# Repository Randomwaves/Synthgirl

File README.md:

# Synthgirl

**A touch-controlled hardware wavetable synthesizer** — dual-oscillator synth engine and DSP effects built around an STM32H723 (Cortex-M7), with a 480×854 color display, a fully capacitive-touch control surface, and MIDI/Sync I/O.

This repository holds the complete hardware design (Eagle/KiCad) and firmware (STM32CubeIDE / C++) for Synthgirl, released by [Randomwaves](https://randomwaves.io) as an open hardware/software project. Synthgirl shares its platform, DSP chain, and touch-based control surface with [Drumboy](https://github.com/Randomwaves/Drumboy), built around a dual-oscillator wavetable engine instead of a sample-layer sequencer.

---

## Overview

The MCU sits at the center of the same core subsystems as Drumboy: an NT35510 display over a 16-bit parallel GPIO bus, external SDRAM on the FMC bus for wavetable storage, an SGTL5000 audio codec over I2S/I2C, a microSD card over SDMMC2 for storage, and MIDI/Sync connectivity over USART/GPIO. The control surface is driven entirely by three capacitive-touch channels.

| | |
|---|---|
| **MCU** | STM32H723ZGT6 — Cortex-M7, LQFP-144 |
| **Display** | NT35510, 480×854, 16-bit parallel |
| **SDRAM** | External, FMC bus (wavetable storage) |
| **Audio codec** | SGTL5000 — I2S3 audio / I2C3 control |
| **Storage** | microSD, SDMMC2, FAT filesystem |
| **Control surface** | 3× capacitive-touch channels (CT0–CT2) |
| **Connectivity** | MIDI In/Out, Sync In/Out |
| **Firmware** | v1.05 |

## Features

- **Dual-oscillator wavetable engine** (Osc A / Osc B), each with independent LFO modulation
- **9 effect types** per send slot: Delay, Chorus, Flanger, Phaser, Compressor, Expander, Overdrive, Distortion, Bitcrusher
- **2 multimode filters + 2 send effects + stereo reverb** in the DSP chain
- **Built-in step sequencer** alongside live/MIDI note input
- **MIDI In/Out** and **Sync In/Out** for external clock/gate sync
- **SD-card firmware updates** via a dedicated bootloader, mirroring the same two-project split as Drumboy

## Repository structure

```
01 Hardware/
  Main/       Main board — Eagle CAD (Main.sch / Main.brd)
  Top/        Top/control-surface board — Eagle CAD (Top.sch / Top.brd)
  Connector/  Interconnect board — KiCad (migrated from Eagle)
  Bottom/     Base board — KiCad (migrated from Eagle)

02 Software/
  Synthgirl-Boot-H723/   Bootloader — STM32CubeIDE project
  Synthgirl-App-H723/    Application firmware — STM32CubeIDE project
  Firmware/               Prebuilt firmware binaries
  Sd Card/                Reference SD card contents (wavetables, presets, system data)
```

## Hardware

Main and Top were originally designed in **Autodesk Eagle** (`.sch` / `.brd`); Connector and Bottom have since been migrated to **KiCad**.

## Firmware

Built with **STM32CubeIDE**, written in C/C++ against the STM32 HAL. Firmware is split into `Synthgirl-Boot-H723` (bootloader) and `Synthgirl-App-H723` (application), sharing one flash device — the same split used across Randomwaves' STM32H723 instruments.

## License

Released under the [MIT License](LICENSE).

## Community

- 💬 [Discord community](https://discord.gg/5atevNH6UU) — join the discussion
- 🌐 [randomwaves.io](https://www.randomwaves.io)
- ✉️ [hello@randomwaves.io](mailto:hello@randomwaves.io)

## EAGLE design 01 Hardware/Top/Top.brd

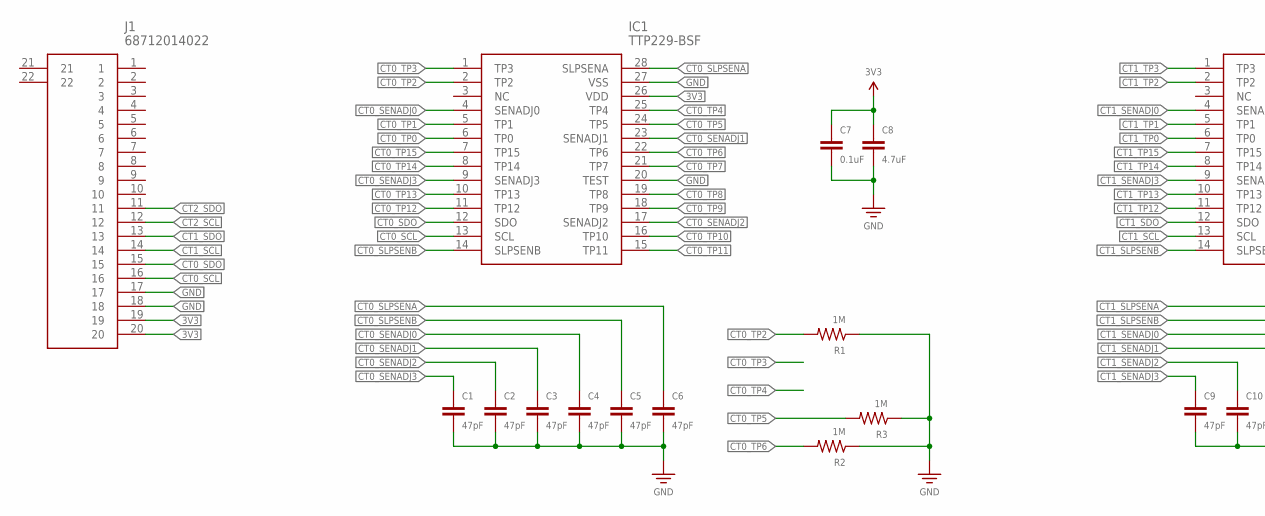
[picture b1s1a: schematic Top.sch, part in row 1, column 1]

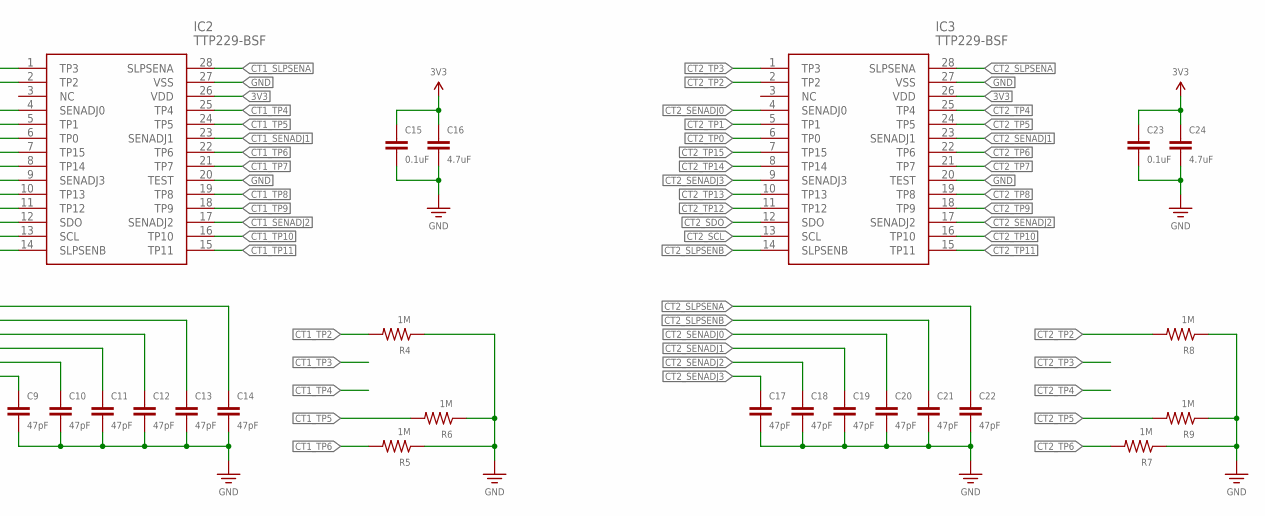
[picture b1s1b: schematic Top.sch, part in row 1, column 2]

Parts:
C1, C2, C3, C4, C5, C6, C9, C10, C11, C12, C13, C14, C17, C18, C19, C20, C21, C22: 47pF; CAP-0603
C7, C15, C23: 0.1uF; CAP-0603
C8, C16, C24: 4.7uF; CAP-0603
IC1, IC2, IC3: TTP229-BSF; SOP64P600X175-28N
J1: 68712014022
R1, R2, R3, R4, R5, R6, R7, R8, R9: 1M; RES-0603

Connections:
3V3: C7.P$1 (1), C8.P$1 (1), C15.P$1 (1), C16.P$1 (1), C23.P$1 (1), C24.P$1 (1), IC1.26 (VDD), IC2.26 (VDD), IC3.26 (VDD), J1.19, J1.20
CT0_SCL: IC1.13 (SCL), J1.16
CT0_SDO: IC1.12 (SDO), J1.15
CT0_SENADJ0: C4.P$1 (1), IC1.4 (SENADJ0)
CT0_SENADJ1: C3.P$1 (1), IC1.23 (SENADJ1)
CT0_SENADJ2: C2.P$1 (1), IC1.17 (SENADJ2)
CT0_SENADJ3: C1.P$1 (1), IC1.9 (SENADJ3)
CT0_SLPSENA: C6.P$1 (1), IC1.28 (SLPSENA)
CT0_SLPSENB: C5.P$1 (1), IC1.14 (SLPSENB)
CT0_TP0: IC1.6 (TP0)
CT0_TP1: IC1.5 (TP1)
CT0_TP2: IC1.2 (TP2), R1.P$2 (2)
CT0_TP3: IC1.1 (TP3)
CT0_TP4: IC1.25 (TP4)
CT0_TP5: IC1.24 (TP5), R3.P$2 (2)
CT0_TP6: IC1.22 (TP6), R2.P$2 (2)
CT0_TP7: IC1.21 (TP7)
CT0_TP8: IC1.19 (TP8)
CT0_TP9: IC1.18 (TP9)
CT0_TP10: IC1.16 (TP10)
CT0_TP11: IC1.15 (TP11)
CT0_TP12: IC1.11 (TP12)
CT0_TP13: IC1.10 (TP13)
CT0_TP14: IC1.8 (TP14)
CT0_TP15: IC1.7 (TP15)
CT1_SCL: IC2.13 (SCL), J1.14
CT1_SDO: IC2.12 (SDO), J1.13
CT1_SENADJ0: C12.P$1 (1), IC2.4 (SENADJ0)
CT1_SENADJ1: C11.P$1 (1), IC2.23 (SENADJ1)
CT1_SENADJ2: C10.P$1 (1), IC2.17 (SENADJ2)
CT1_SENADJ3: C9.P$1 (1), IC2.9 (SENADJ3)
CT1_SLPSENA: C14.P$1 (1), IC2.28 (SLPSENA)
CT1_SLPSENB: C13.P$1 (1), IC2.14 (SLPSENB)
CT1_TP0: IC2.6 (TP0)
CT1_TP1: IC2.5 (TP1)
CT1_TP2: IC2.2 (TP2), R4.P$2 (2)
CT1_TP3: IC2.1 (TP3)
CT1_TP4: IC2.25 (TP4)
CT1_TP5: IC2.24 (TP5), R6.P$2 (2)
CT1_TP6: IC2.22 (TP6), R5.P$2 (2)
CT1_TP7: IC2.21 (TP7)
CT1_TP8: IC2.19 (TP8)
CT1_TP9: IC2.18 (TP9)
CT1_TP10: IC2.16 (TP10)
CT1_TP11: IC2.15 (TP11)
CT1_TP12: IC2.11 (TP12)
CT1_TP13: IC2.10 (TP13)
CT1_TP14: IC2.8 (TP14)
CT1_TP15: IC2.7 (TP15)
CT2_SCL: IC3.13 (SCL), J1.12
CT2_SDO: IC3.12 (SDO), J1.11
CT2_SENADJ0: C20.P$1 (1), IC3.4 (SENADJ0)
CT2_SENADJ1: C19.P$1 (1), IC3.23 (SENADJ1)
CT2_SENADJ2: C18.P$1 (1), IC3.17 (SENADJ2)
CT2_SENADJ3: C17.P$1 (1), IC3.9 (SENADJ3)
CT2_SLPSENA: C22.P$1 (1), IC3.28 (SLPSENA)
CT2_SLPSENB: C21.P$1 (1), IC3.14 (SLPSENB)
CT2_TP0: IC3.6 (TP0)
CT2_TP1: IC3.5 (TP1)
CT2_TP2: IC3.2 (TP2), R8.P$2 (2)
CT2_TP3: IC3.1 (TP3)
CT2_TP4: IC3.25 (TP4)
CT2_TP5: IC3.24 (TP5), R9.P$2 (2)
CT2_TP6: IC3.22 (TP6), R7.P$2 (2)
CT2_TP7: IC3.21 (TP7)
CT2_TP8: IC3.19 (TP8)
CT2_TP9: IC3.18 (TP9)
CT2_TP10: IC3.16 (TP10)
CT2_TP11: IC3.15 (TP11)
CT2_TP12: IC3.11 (TP12)
CT2_TP13: IC3.10 (TP13)
CT2_TP14: IC3.8 (TP14)
CT2_TP15: IC3.7 (TP15)
GND: C1.P$2 (2), C2.P$2 (2), C3.P$2 (2), C4.P$2 (2), C5.P$2 (2), C6.P$2 (2), C7.P$2 (2), C8.P$2 (2), C9.P$2 (2), C10.P$2 (2), C11.P$2 (2), C12.P$2 (2), C13.P$2 (2), C14.P$2 (2), C15.P$2 (2), C16.P$2 (2), C17.P$2 (2), C18.P$2 (2), C19.P$2 (2), C20.P$2 (2), C21.P$2 (2), C22.P$2 (2), C23.P$2 (2), C24.P$2 (2), IC1.20 (TEST), IC1.27 (VSS), IC2.20 (TEST), IC2.27 (VSS), IC3.20 (TEST), IC3.27 (VSS), J1.17, J1.18, R1.P$1 (1), R2.P$1 (1), R3.P$1 (1), R4.P$1 (1), R5.P$1 (1), R6.P$1 (1), R7.P$1 (1), R8.P$1 (1), R9.P$1 (1)

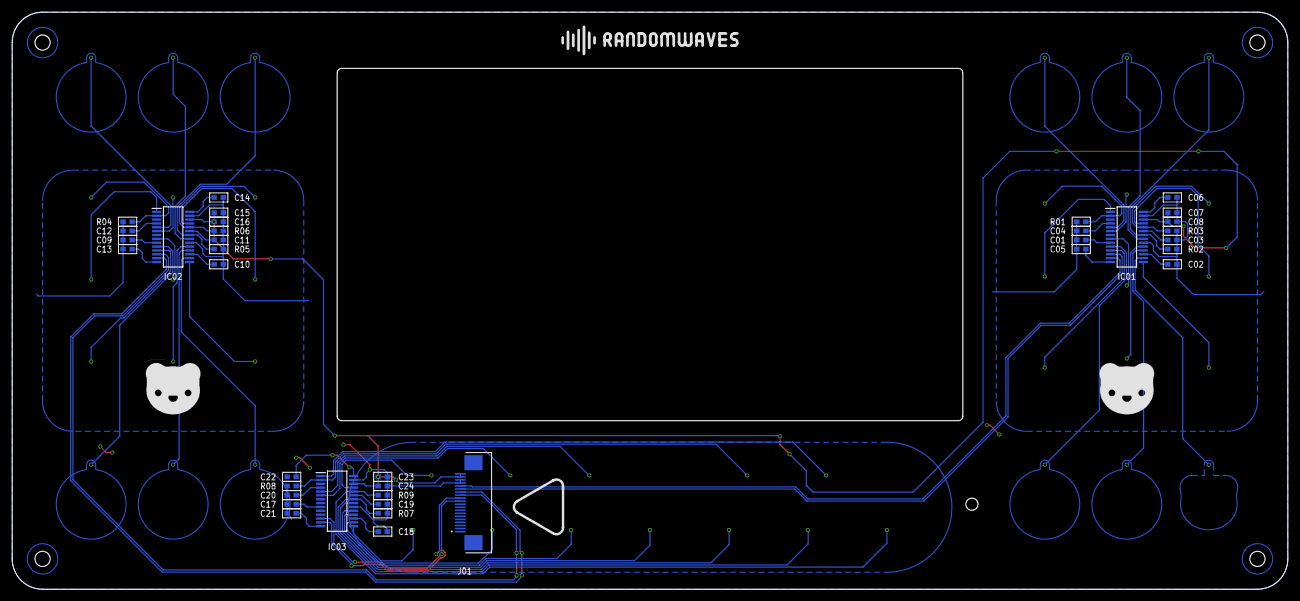
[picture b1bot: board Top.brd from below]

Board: 2 copper layers, 210.0 x 95.0 mm, 37 parts (37 on the bottom side), 35 nets.

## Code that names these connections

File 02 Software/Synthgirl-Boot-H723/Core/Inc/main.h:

/* USER CODE BEGIN Header */
/**
  ******************************************************************************
  * @file           : main.h
  * @brief          : Header for main.c file.
  *                   This file contains the common defines of the application.
  ******************************************************************************
  * @attention
  *
  * Copyright (c) 2023 STMicroelectronics.
  * All rights reserved.
  *
  * This software is licensed under terms that can be found in the LICENSE file
  * in the root directory of this software component.
  * If no LICENSE file comes with this software, it is provided AS-IS.
  *
  ******************************************************************************
  */
/* USER CODE END Header */

/* Define to prevent recursive inclusion -------------------------------------*/
#ifndef __MAIN_H
#define __MAIN_H

#ifdef __cplusplus
extern "C" {
#endif

/* Includes ------------------------------------------------------------------*/
#include "stm32h7xx_hal.h"

/* Private includes ----------------------------------------------------------*/
/* USER CODE BEGIN Includes */

/* USER CODE END Includes */

/* Exported types ------------------------------------------------------------*/
/* USER CODE BEGIN ET */

/* USER CODE END ET */

/* Exported constants --------------------------------------------------------*/
/* USER CODE BEGIN EC */

/* USER CODE END EC */

/* Exported macro ------------------------------------------------------------*/
/* USER CODE BEGIN EM */

/* USER CODE END EM */

/* Exported functions prototypes ---------------------------------------------*/
void Error_Handler(void);

/* USER CODE BEGIN EFP */

/* USER CODE END EFP */

/* Private defines -----------------------------------------------------------*/
#define CT2_SCL_Pin GPIO_PIN_2
#define CT2_SCL_GPIO_Port GPIOE
#define SDMMC2_DETECT_Pin GPIO_PIN_13
#define SDMMC2_DETECT_GPIO_Port GPIOC
#define BUTTON_Pin GPIO_PIN_10
#define BUTTON_GPIO_Port GPIOF
#define BUTTON_EXTI_IRQn EXTI15_10_IRQn
#define CT0_SCL_Pin GPIO_PIN_0
#define CT0_SCL_GPIO_Port GPIOA
#define CT0_SDO_Pin GPIO_PIN_1
#define CT0_SDO_GPIO_Port GPIOA
#define CT0_SDO_EXTI_IRQn EXTI1_IRQn
#define CT1_SCL_Pin GPIO_PIN_2
#define CT1_SCL_GPIO_Port GPIOA
#define CT1_SDO_Pin GPIO_PIN_3
#define CT1_SDO_GPIO_Port GPIOA
#define CT1_SDO_EXTI_IRQn EXTI3_IRQn
#define CT2_SDO_Pin GPIO_PIN_7
#define CT2_SDO_GPIO_Port GPIOA
#define CT2_SDO_EXTI_IRQn EXTI9_5_IRQn
#define LCD_D0_Pin GPIO_PIN_0
#define LCD_D0_GPIO_Port GPIOB
#define LCD_D1_Pin GPIO_PIN_1
#define LCD_D1_GPIO_Port GPIOB
#define LCD_D2_Pin GPIO_PIN_2
#define LCD_D2_GPIO_Port GPIOB
#define LCD_D10_Pin GPIO_PIN_10
#define LCD_D10_GPIO_Port GPIOB
#define LCD_D11_Pin GPIO_PIN_11
#define LCD_D11_GPIO_Port GPIOB
#define LCD_D12_Pin GPIO_PIN_12
#define LCD_D12_GPIO_Port GPIOB
#define LCD_D13_Pin GPIO_PIN_13
#define LCD_D13_GPIO_Port GPIOB
#define LCD_D14_Pin GPIO_PIN_14
#define LCD_D14_GPIO_Port GPIOB
#define LCD_D15_Pin GPIO_PIN_15
#define LCD_D15_GPIO_Port GPIOB
#define LED0_Pin GPIO_PIN_11
#define LED0_GPIO_Port GPIOD
#define LED1_Pin GPIO_PIN_12
#define LED1_GPIO_Port GPIOD
#define LED2_Pin GPIO_PIN_13
#define LED2_GPIO_Port GPIOD
#define LCD_CS_Pin GPIO_PIN_2
#define LCD_CS_GPIO_Port GPIOD
#define LCD_RD_Pin GPIO_PIN_3
#define LCD_RD_GPIO_Port GPIOD
#define LCD_WR_Pin GPIO_PIN_4
#define LCD_WR_GPIO_Port GPIOD
#define LCD_RS_Pin GPIO_PIN_5
#define LCD_RS_GPIO_Port GPIOD
#define LCD_RESET_Pin GPIO_PIN_13
#define LCD_RESET_GPIO_Port GPIOG
#define LCD_BL_Pin GPIO_PIN_14
#define LCD_BL_GPIO_Port GPIOG
#define LCD_D3_Pin GPIO_PIN_3
#define LCD_D3_GPIO_Port GPIOB
#define LCD_D4_Pin GPIO_PIN_4
#define LCD_D4_GPIO_Port GPIOB
#define LCD_D5_Pin GPIO_PIN_5
#define LCD_D5_GPIO_Port GPIOB
#define LCD_D6_Pin GPIO_PIN_6
#define LCD_D6_GPIO_Port GPIOB
#define LCD_D7_Pin GPIO_PIN_7
#define LCD_D7_GPIO_Port GPIOB
#define LCD_D8_Pin GPIO_PIN_8
#define LCD_D8_GPIO_Port GPIOB
#define LCD_D9_Pin GPIO_PIN_9
#define LCD_D9_GPIO_Port GPIOB

/* USER CODE BEGIN Private defines */

/* USER CODE END Private defines */

#ifdef __cplusplus
}
#endif

#endif /* __MAIN_H */

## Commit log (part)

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2025-04-04 Release v1.01

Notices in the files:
parts and their libraries:
Power: Licensing: Creative Commons ShareAlike 4.0 International - https://creativecommons.org/licenses/by-sa/4.0
